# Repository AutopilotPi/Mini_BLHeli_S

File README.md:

# Mini_BLHeli_S

The repo is a hardware design for BLHeli BLDC Driver(https://github.com/bitdump/BLHeli) by Kicad 6.0. The design aim to construct a 
SMT module which could be integrated into PCB of Flight Controller or some other DIY projects easily. 

- Pinout class: J
- freq class: H (48Mhz)
- delay class : above 20
- mos: N + P (so there are no mos drivers)
- voltage: 1s-3s(which is limited by LDO, if you use the input 3V3 and don't solder the LDO, then you could use higher voltage. Please be care about withstand voltage of 
input capacities) 

## License
Please notice that the license of this project is GPL 3.0. For hardware project, hope that you can share the changes if you make something different in the sch or pcb.

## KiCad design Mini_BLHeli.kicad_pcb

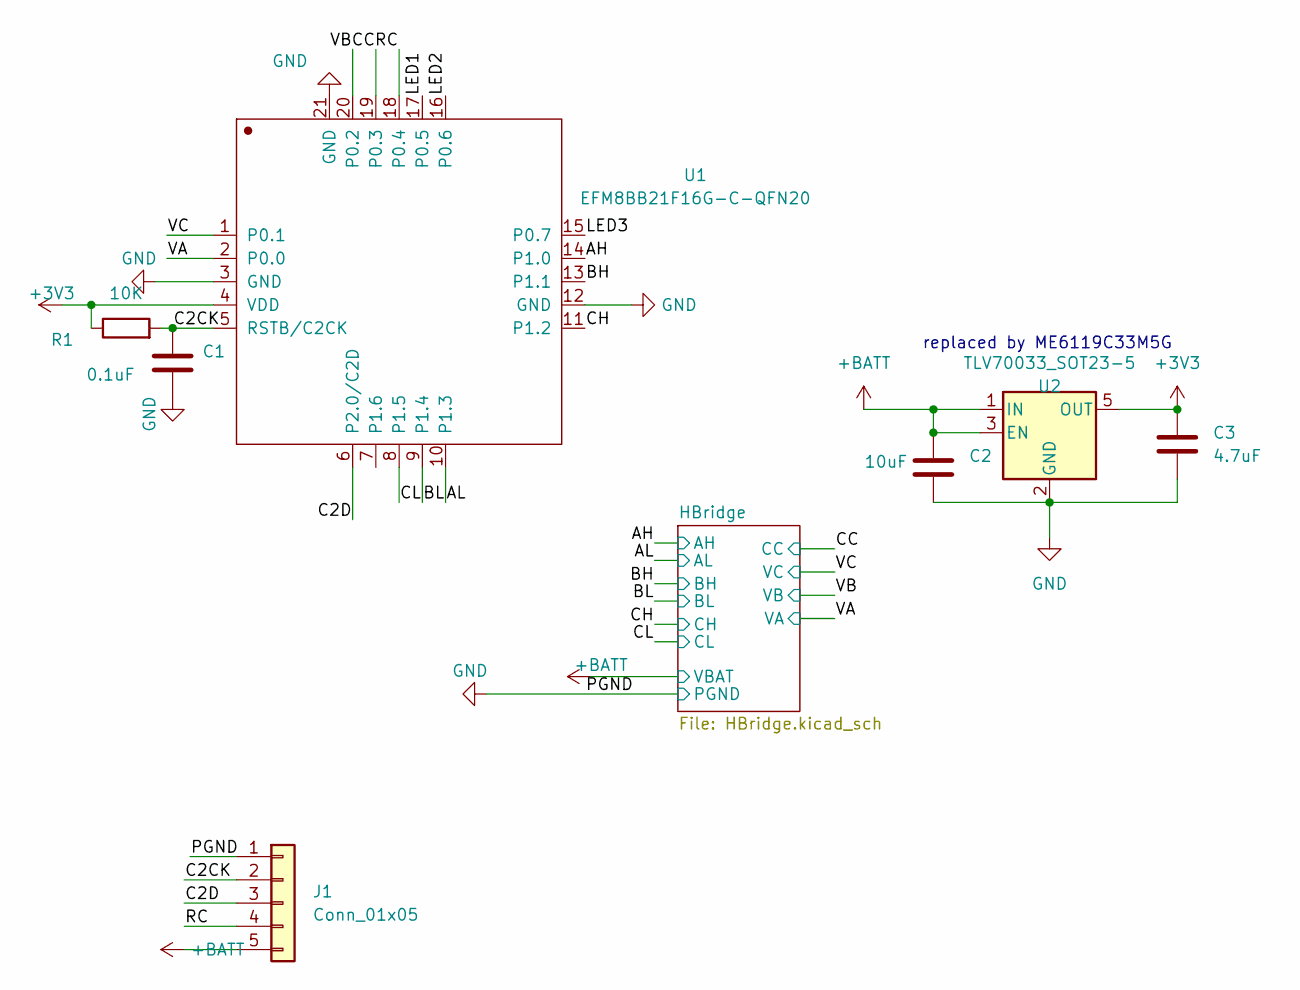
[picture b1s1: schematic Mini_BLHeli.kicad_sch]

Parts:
C1: 0.1uF; C_0402_1005Metric
C2: 10uF; C_0805_2012Metric
C3: 4.7uF; C_0402_1005Metric
J1: Conn_01x05; PinHeader_1x05_P2.54mm_Vertical
R1: 10K; R_0402_1005Metric
U1: EFM8BB21F16G-C-QFN20; SiliconLabs_QFN-20-1EP_3x3mm_P0.5mm_EP1.8x1.8mm
U2: TLV70033_SOT23-5; SOT-23-5

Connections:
+3V3: C3.1, R1.1, U1.4 (VDD), U2.5 (OUT)
+BATT: C2.1, J1.5, U2.1 (IN), U2.3 (EN); also elsewhere on the board
/AH: U1.14 (P1.0); also elsewhere on the board
/AL: U1.10 (P1.3); also elsewhere on the board
/BH: U1.13 (P1.1); also elsewhere on the board
/BL: U1.9 (P1.4); also elsewhere on the board
/C2CK: C1.1, J1.2, R1.2, U1.5 (RSTB/C2CK)
/C2D: J1.3, U1.6 (P2.0/C2D)
/CC: U1.19 (P0.3); also elsewhere on the board
/CH: U1.11 (P1.2); also elsewhere on the board
/CL: U1.8 (P1.5); also elsewhere on the board
/LED1: U1.17 (P0.5)
/LED2: U1.16 (P0.6)
/LED3: U1.15 (P0.7)
/RC: J1.4, U1.18 (P0.4)
/VA: U1.2 (P0.0); also elsewhere on the board
/VB: U1.20 (P0.2); also elsewhere on the board
/VC: U1.1 (P0.1); also elsewhere on the board
GND: C1.2, C2.2, C3.2, J1.1, U1.3 (GND), U1.12 (GND), U1.21 (GND), U2.2 (GND); also elsewhere on the board

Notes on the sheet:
replaced by ME6119C33M5G

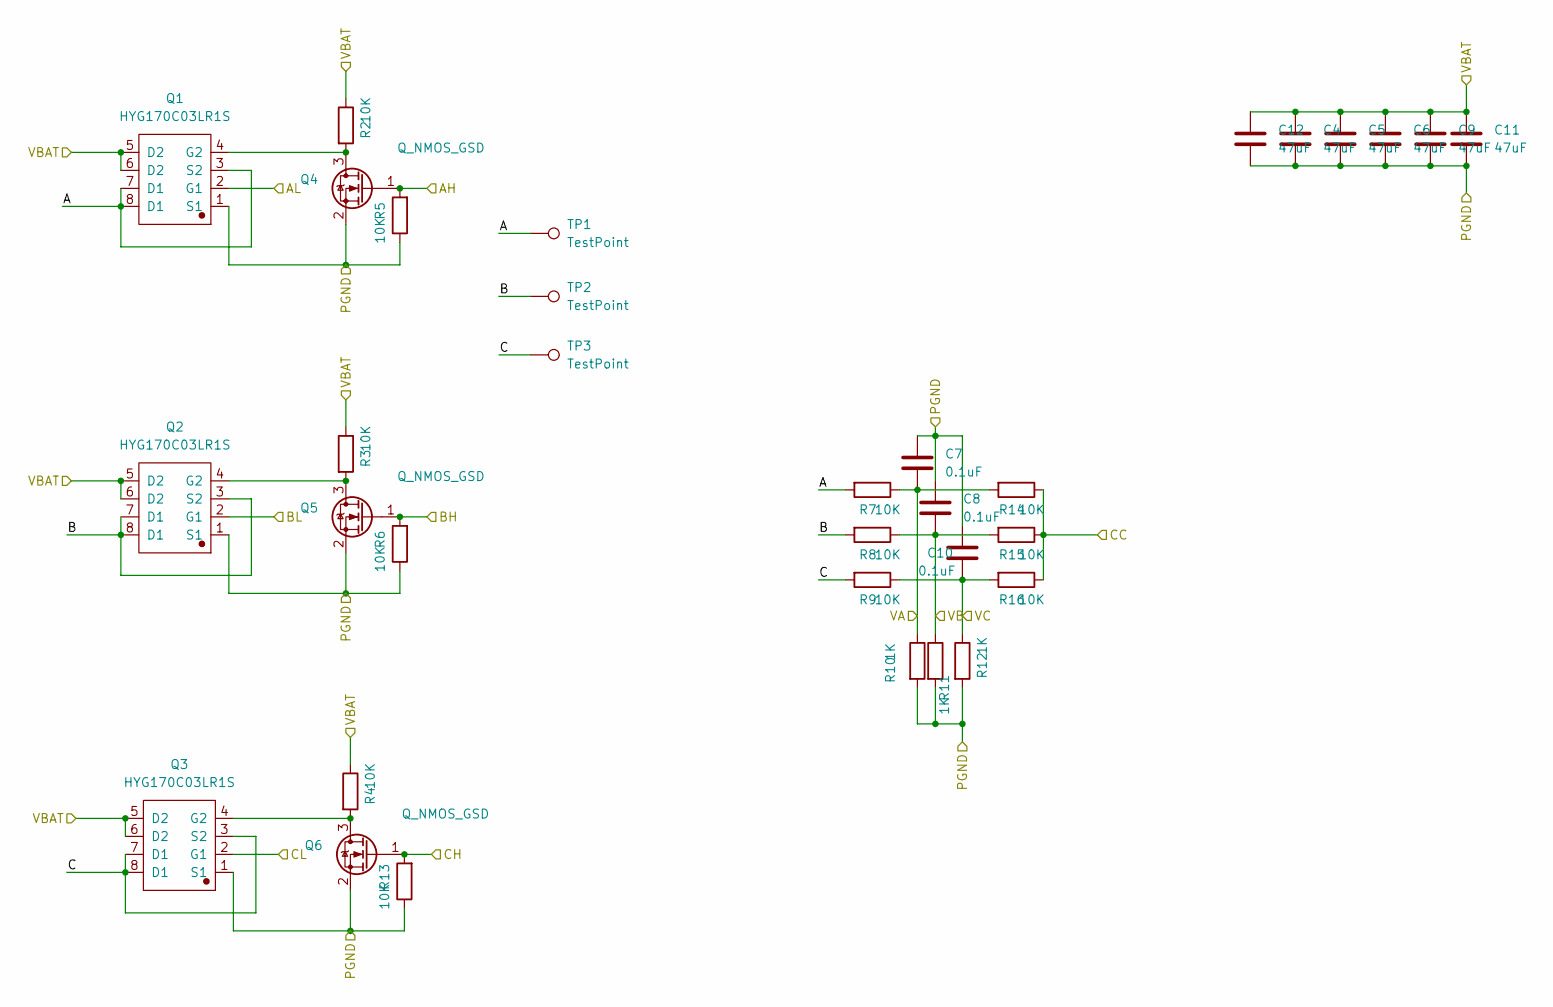
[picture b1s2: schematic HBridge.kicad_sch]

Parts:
C4, C5, C6, C9, C11, C12: 47uF; C_1206_3216Metric
C7, C8, C10: 0.1uF; C_0402_1005Metric
Q1, Q2, Q3: HYG170C03LR1S; SO-8_3.9x4.9mm_P1.27mm
Q4, Q5, Q6: Q_NMOS_GSD; SOT-23
R2, R3, R4, R5, R6, R7, R8, R9, R13, R14, R15, R16: 10K; R_0402_1005Metric
R10, R11, R12: 1K; R_0402_1005Metric
TP1, TP2, TP3: TestPoint; TestPoint_THTPad_2.0x2.0mm_Drill1.0mm

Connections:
+BATT: C4.1, C5.1, C6.1, C9.1, C11.1, C12.1, Q1.5 (D2), Q1.6 (D2), Q2.5 (D2), Q2.6 (D2), Q3.5 (D2), Q3.6 (D2), R2.1, R3.1, R4.1; also elsewhere on the board
/AH: Q4.1 (G), R5.2; also elsewhere on the board
/AL: Q1.2 (G1); also elsewhere on the board
/BH: Q5.1 (G), R6.2; also elsewhere on the board
/BL: Q2.2 (G1); also elsewhere on the board
/CC: R14.1, R15.1, R16.1; also elsewhere on the board
/CH: Q6.1 (G), R13.2; also elsewhere on the board
/CL: Q3.2 (G1); also elsewhere on the board
/HBridge/A: Q1.3 (S2), Q1.7 (D1), Q1.8 (D1), R7.2, TP1.1
/HBridge/B: Q2.3 (S2), Q2.7 (D1), Q2.8 (D1), R8.2, TP2.1
/HBridge/C: Q3.3 (S2), Q3.7 (D1), Q3.8 (D1), R9.2, TP3.1
/VA: C7.1, R7.1, R10.1, R14.2; also elsewhere on the board
/VB: C8.1, R8.1, R11.1, R15.2; also elsewhere on the board
/VC: C10.1, R9.1, R12.1, R16.2; also elsewhere on the board
GND: C4.2, C5.2, C6.2, C7.2, C8.2, C9.2, C10.2, C11.2, C12.2, Q1.1 (S1), Q2.1 (S1), Q3.1 (S1), Q4.2 (S), Q5.2 (S), Q6.2 (S), R5.1, R6.1, R10.2, R11.2, R12.2, R13.1; also elsewhere on the board
unnamed: Q1.4 (G2), Q4.3 (D), R2.2
unnamed: Q2.4 (G2), Q5.3 (D), R3.2
unnamed: Q3.4 (G2), Q6.3 (D), R4.2

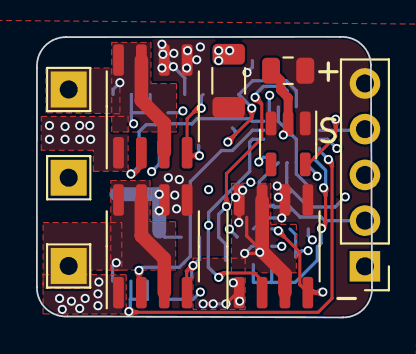
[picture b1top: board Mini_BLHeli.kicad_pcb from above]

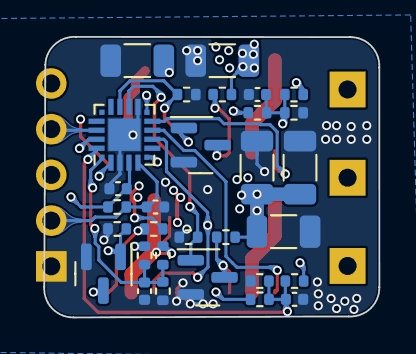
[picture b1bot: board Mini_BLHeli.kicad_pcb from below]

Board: 4 copper layers, 18.6 x 15.6 mm, 40 parts (30 on the bottom side), 22 nets.

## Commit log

2022-04-04 init
2022-04-04 v0.9 finish
2022-04-05 add images
2022-04-05 add docs
2022-08-18 update for new version
